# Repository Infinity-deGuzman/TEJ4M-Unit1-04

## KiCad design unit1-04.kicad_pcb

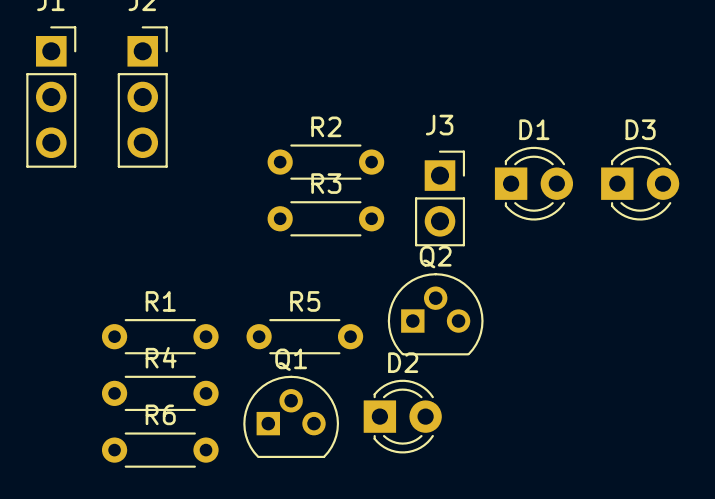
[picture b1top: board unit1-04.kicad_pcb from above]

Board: 2 copper layers, 14 parts (0 on the bottom side), 8 nets, no tracks yet.

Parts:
D1, D2, D3: LED; LED_D3.0mm
J1, J2: XLR3_Switched; PinSocket_1x03_P2.54mm_Vertical
J3: Conn_01x02_Female; PinSocket_1x02_P2.54mm_Vertical
Q1, Q2: 2N3904; TO-92
R1, R2, R3, R4, R5, R6: R_US; R_Axial_DIN0204_L3.6mm_D1.6mm_P5.08mm_Horizontal

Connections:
unnamed: D1.1, J3.1, Q1.1, Q2.1, R6.2
unnamed: D1.2, R3.1
unnamed: D2.1, J3.2, R5.1
unnamed: D2.2, R4.1
unnamed: D3.1, R6.1
unnamed: D3.2, Q1.3, Q2.3, R5.2
unnamed: Q1.2, R1.2, R3.2
unnamed: Q2.2, R2.2, R4.2

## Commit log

2023-11-15 just in case -> for home
2023-11-17 reupload
